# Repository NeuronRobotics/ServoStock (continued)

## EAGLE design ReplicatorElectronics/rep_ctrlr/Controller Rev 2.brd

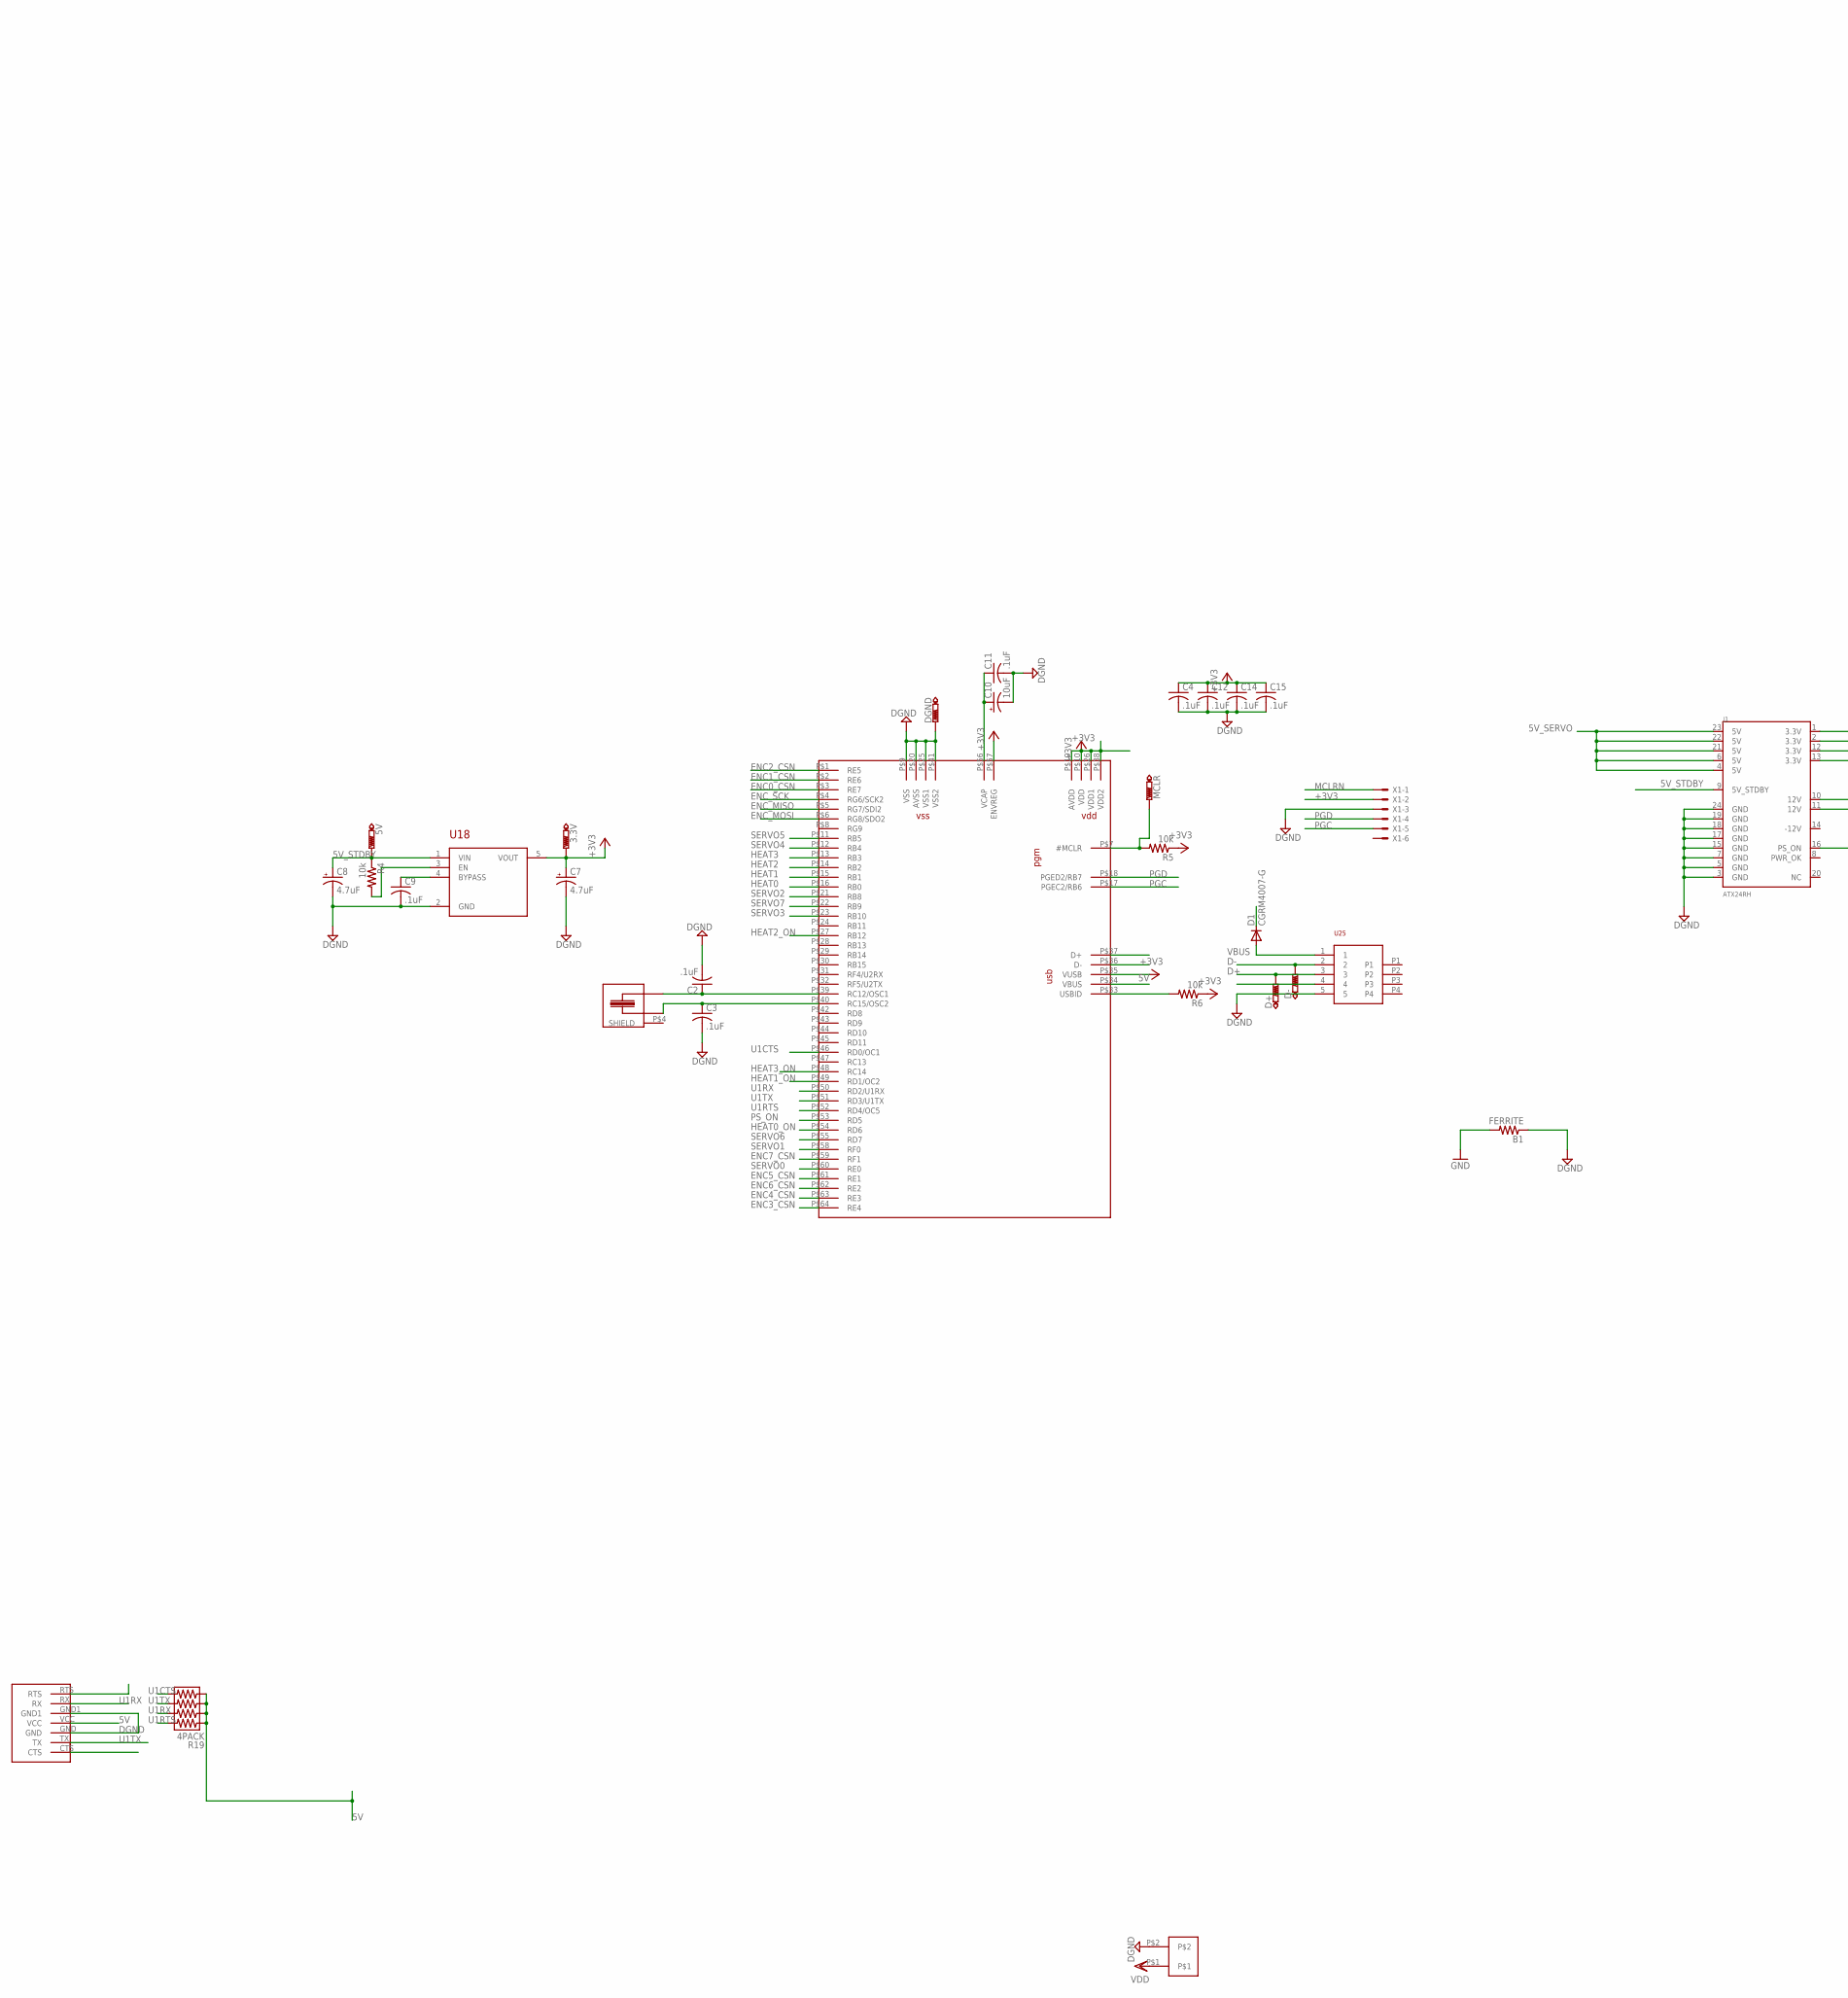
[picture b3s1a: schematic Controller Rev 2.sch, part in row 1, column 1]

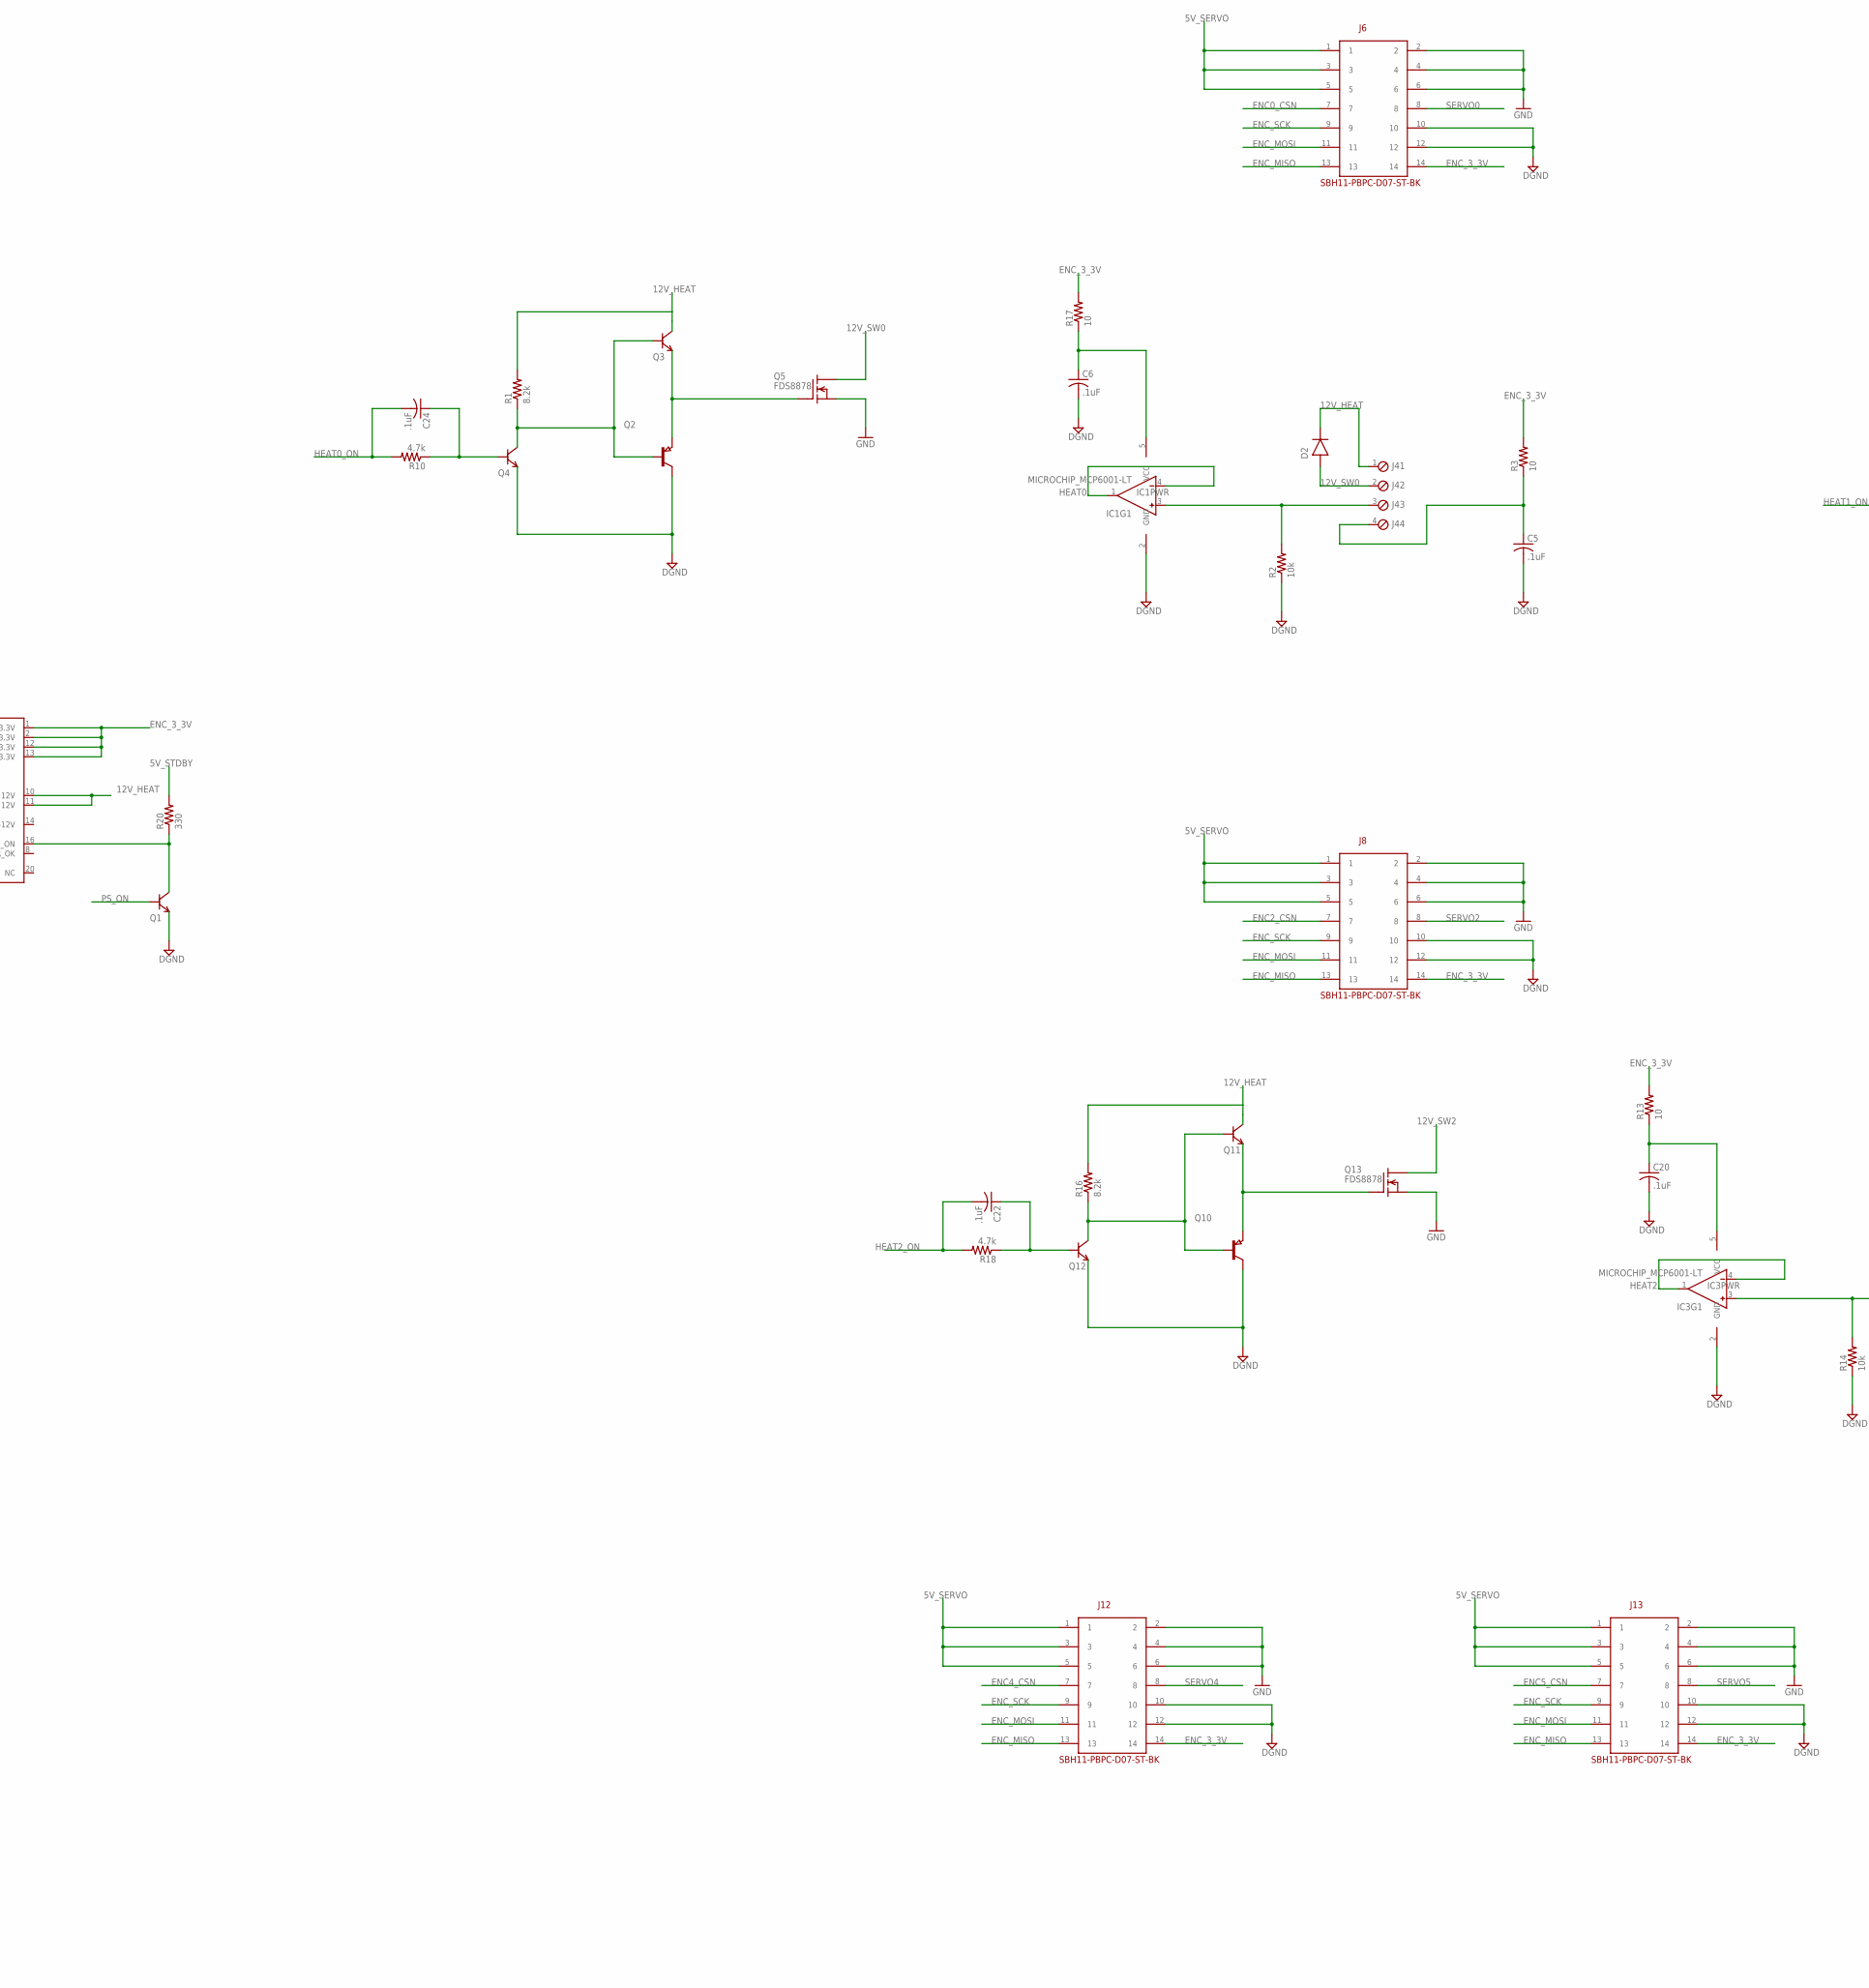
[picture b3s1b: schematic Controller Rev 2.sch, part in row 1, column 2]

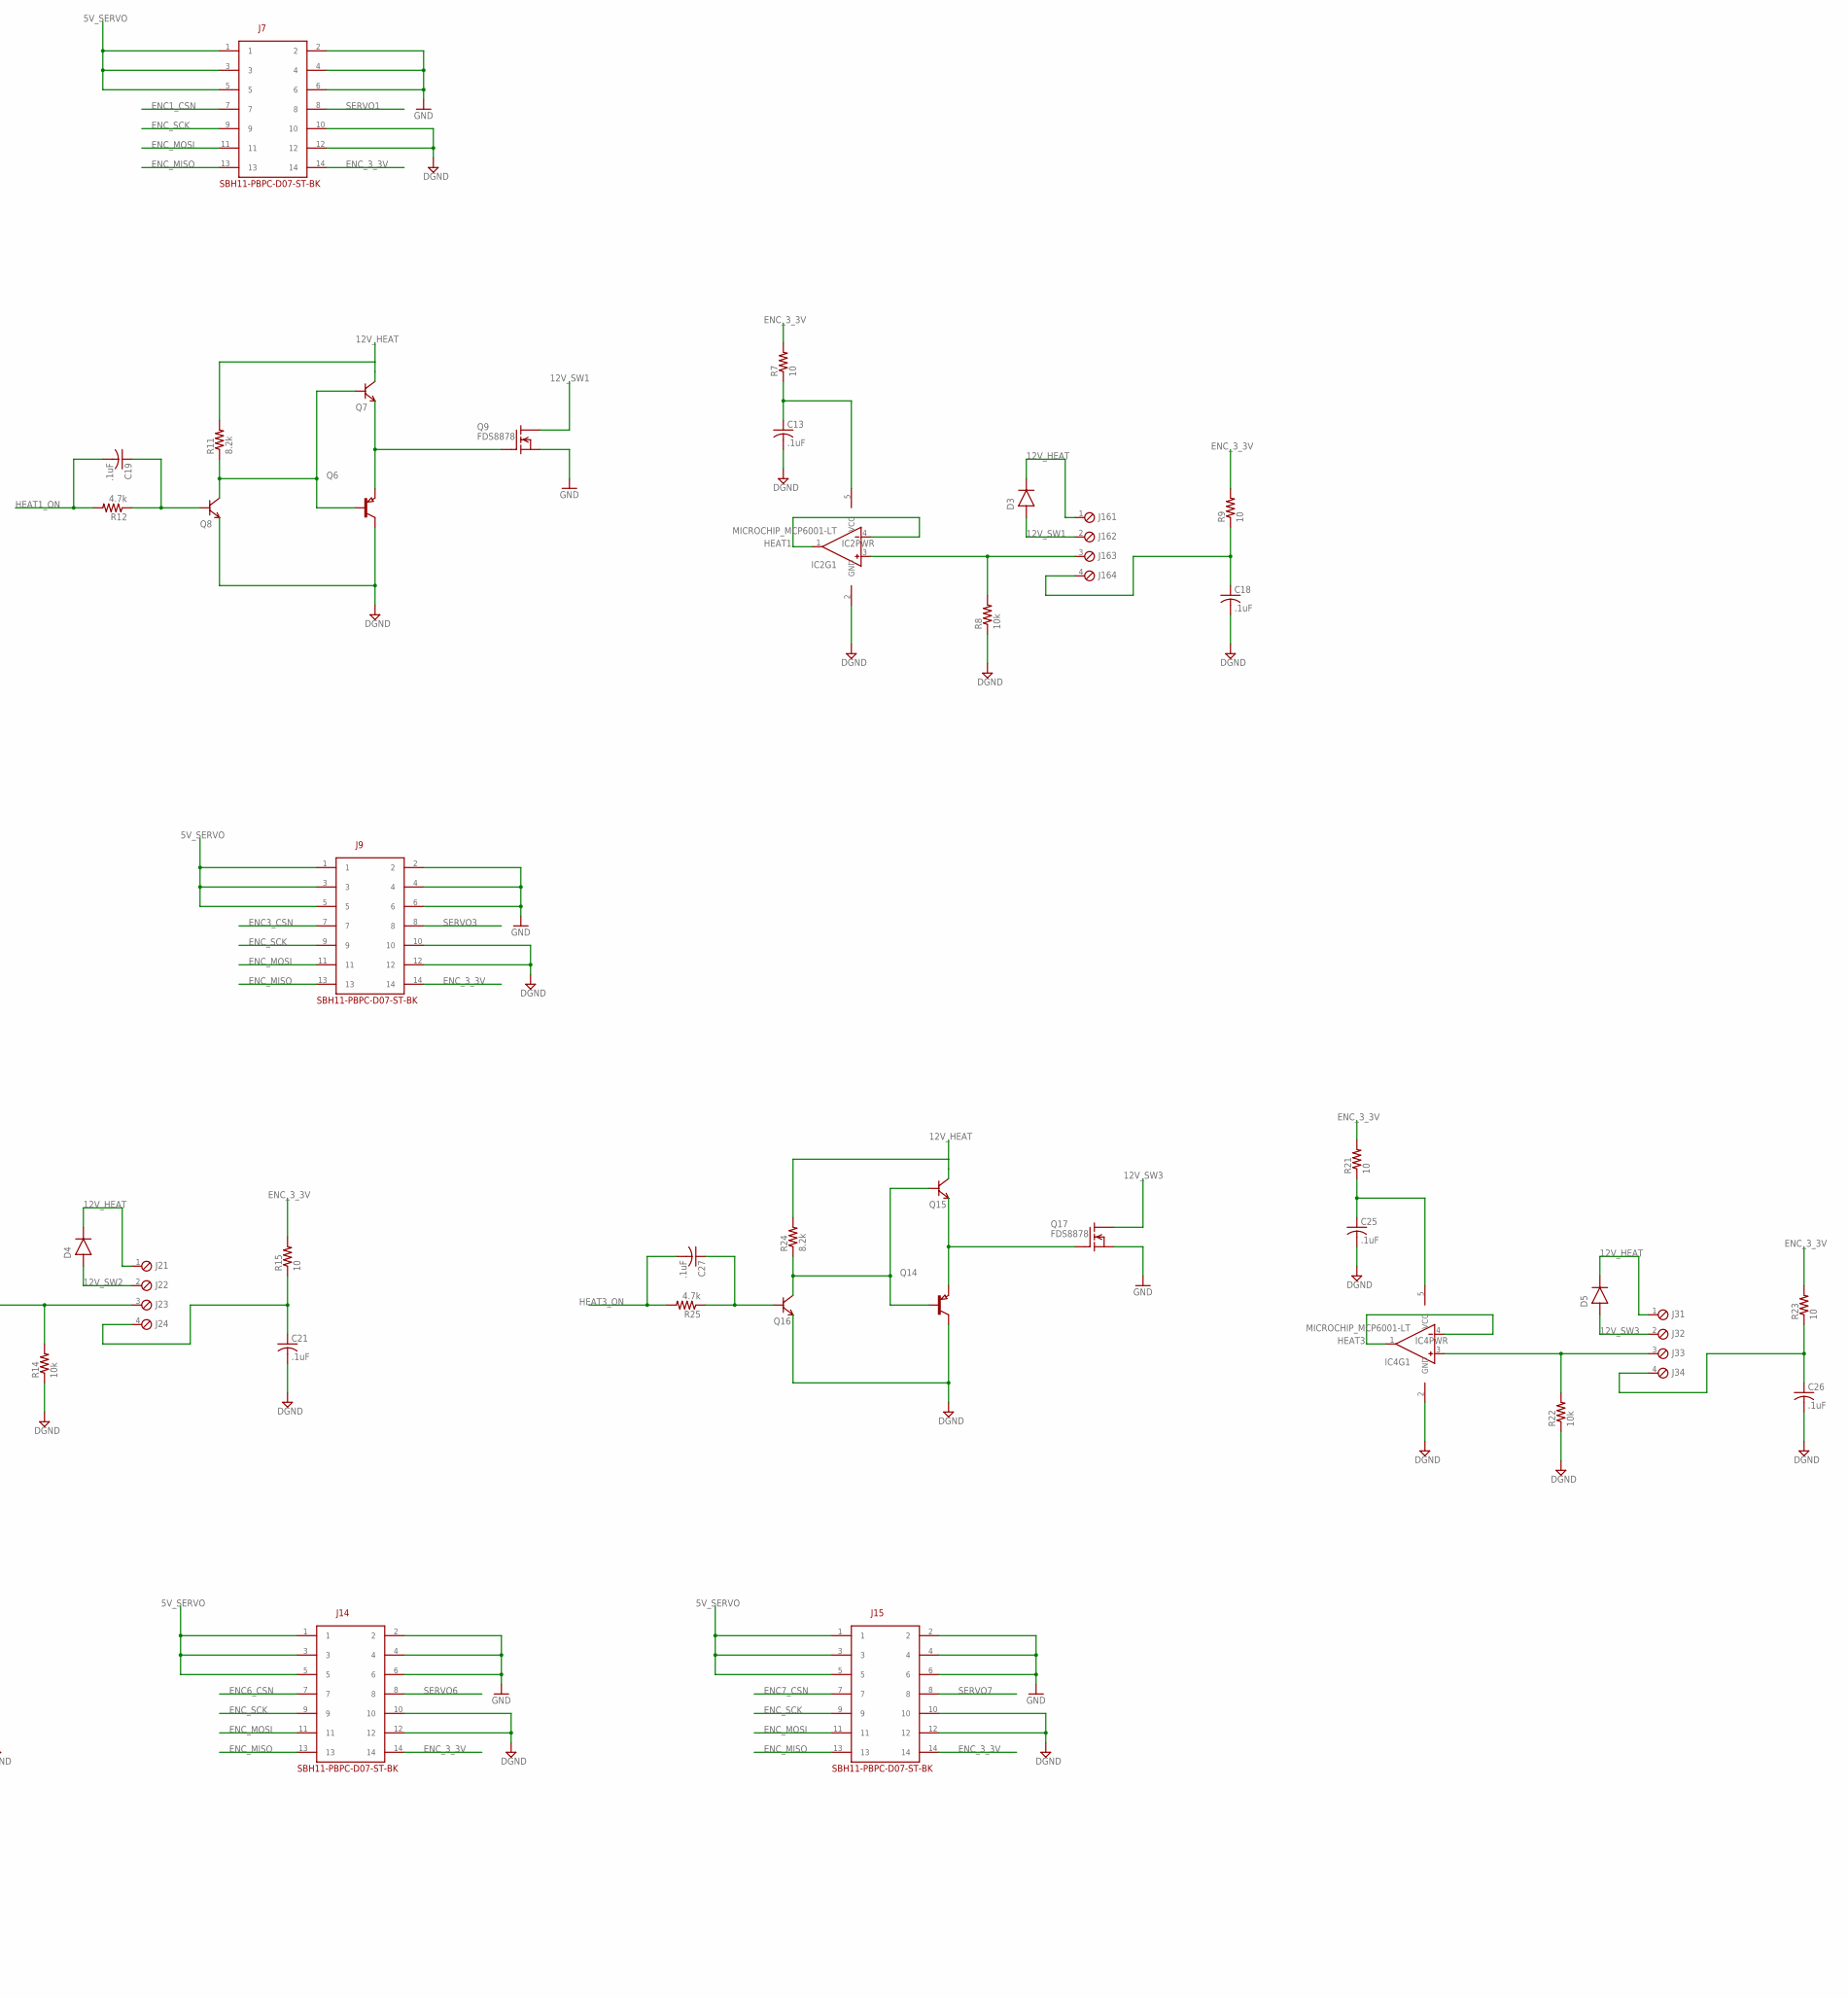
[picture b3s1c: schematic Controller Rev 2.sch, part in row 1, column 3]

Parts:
3.3V, 5V: PTR1TP14R; TP14R
B1: FERRITE; R0603
C2, C3, C4, C5, C6, C11, C12, C13, C14, C15, C18, C19, C20, C21, C22, C24, C25, C26, C27: .1uF; C0603
C7, C8: 4.7uF; R/2012-12R
C9: .1uF; C0402
C10: 10uF; R/2012-12R
D1: CGRM4007-G; SOD-123_MINI-SMA
D2, D3, D4, D5: DISCRETE_DIODESMA; DISCRETE_SMA
D+: PTR1TP14R; TP14R
D-: PTR1TP14R; TP14R
DGND: PTR1B1,27; B1,27
IC1, IC2, IC3, IC4: MICROCHIP_MCP6001-LT; MICROCHIP_SC70-5-LT
J1: ATX24RH; ATX24_RIGHT_ANGLE
J2, J3, J4, J16: OSTVN04A150; 4POL254
J6, J7, J8, J9, J12, J13, J14, J15: SBH11-PBPC-D07-ST-BK
J10: WASP7PIN
MCLR: PTR1TP14R; TP14R
Q1, Q3, Q4, Q7, Q8, Q11, Q12, Q15, Q16: DISCRETE_MMBT3904LT1G; DISCRETE_SOT23
Q2, Q6, Q10, Q14: PNP-TRANSISTOR_SOT23; SOT23
Q5, Q9, Q13, Q17: FDS8878; SO-8
R1, R11, R16, R24: 8.2k; R0603
R2, R5, R6, R8, R14, R22: 10k; R0603
R3, R7, R9, R13, R15, R17, R21, R23: 10; R0603
R4: 10k; R0402
R10, R12, R18, R25: 4.7k; R0603
R19: 4PACK; 4PACK_0603
R20: 330; R0603
U3: PIC32-64TQFP64-2; TQFP64-2
U18: LDS3985XX33; SOT23-5
U25: 1734035-1_USB; 1734035-1_1734035
U$19: 2P; 2PTH
X1: 22-23-2061
X2: CMR3XXT; CMR309T

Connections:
5V: D1.C, J10.VCC, R19.R1B, R19.R2B, R19.R3B, R19.R4B, U3.P$34 (VBUS)
5V_SERVO: J1.4 (5V), J1.6 (5V), J1.21 (5V), J1.22 (5V), J1.23 (5V), J6.1, J6.3, J6.5, J7.1, J7.3, J7.5, J8.1, J8.3, J8.5, J9.1, J9.3, J9.5, J12.1, J12.3, J12.5, J13.1, J13.3, J13.5, J14.1, J14.3, J14.5, J15.1, J15.3, J15.5
5V_STDBY: 5V.TP, C8.+, J1.9 (5V_STDBY), R4.1, R20.2, U18.1 (VIN)
12V_HEAT: D2.C, D3.C, D4.C, D5.C, J1.10 (12V), J1.11 (12V), J2.1, J3.1, J4.1, J16.1, Q3.3 (C), Q7.3 (C), Q11.3 (C), Q15.3 (C), R1.2, R11.2, R16.2, R24.2
12V_SW0: D2.A, J4.2, Q5.5 (D), Q5.6 (D), Q5.7 (D), Q5.8 (D)
12V_SW1: D3.A, J16.2, Q9.5 (D), Q9.6 (D), Q9.7 (D), Q9.8 (D)
12V_SW2: D4.A, J2.2, Q13.5 (D), Q13.6 (D), Q13.7 (D), Q13.8 (D)
12V_SW3: D5.A, J3.2, Q17.5 (D), Q17.6 (D), Q17.7 (D), Q17.8 (D)
+3V3: 3.3V.TP, C4.1, C7.+, C12.1, C14.1, C15.1, R5.1, R6.1, U3.P$10 (VDD), U3.P$19 (AVDD), U3.P$26 (VDD1), U3.P$35 (VUSB), U3.P$38 (VDD2), U3.P$57 (ENVREG), U18.5 (VOUT), X1.2
D+: D+.TP, U3.P$37 (D+), U25.3
D-: D-.TP, U3.P$36 (D-), U25.2
DGND: B1.1, C2.2, C3.2, C4.2, C5.2, C6.2, C7.-, C8.-, C9.2, C10.-, C11.2, C12.2, C13.2, C14.2, C15.2, C18.2, C20.2, C21.2, C25.2, C26.2, DGND.PP, IC1.2 (GND), IC2.2 (GND), IC3.2 (GND), IC4.2 (GND), J1.3 (GND), J1.5 (GND), J1.7 (GND), J1.15 (GND), J1.17 (GND), J1.18 (GND), J1.19 (GND), J1.24 (GND), J6.10, J6.12, J7.10, J7.12, J8.10, J8.12, J9.10, J9.12, J10.GND, J10.GND1, J12.10, J12.12, J13.10, J13.12, J14.10, J14.12, J15.10, J15.12, Q1.2 (E), Q2.3 (C), Q4.2 (E), Q6.3 (C), Q8.2 (E), Q10.3 (C), Q12.2 (E), Q14.3 (C), Q16.2 (E), R2.1, R8.1, R14.1, R22.1, U3.P$9 (VSS), U3.P$20 (AVSS), U3.P$25 (VSS1), U3.P$41 (VSS2), U18.2 (GND), U25.5, U$19.P$2, X1.3
ENC0_CSN: J6.7, U3.P$3 (RE7)
ENC1_CSN: J7.7, U3.P$2 (RE6)
ENC2_CSN: J8.7, U3.P$1 (RE5)
ENC3_CSN: J9.7, U3.P$64 (RE4)
ENC4_CSN: J12.7, U3.P$63 (RE3)
ENC5_CSN: J13.7, U3.P$61 (RE1)
ENC6_CSN: J14.7, U3.P$62 (RE2)
ENC7_CSN: J15.7, U3.P$59 (RF1)
ENC_3_3V: J1.1 (3.3V), J1.2 (3.3V), J1.12 (3.3V), J1.13 (3.3V), J6.14, J7.14, J8.14, J9.14, J12.14, J13.14, J14.14, J15.14, R3.2, R7.2, R9.2, R13.2, R15.2, R17.2, R21.2, R23.2
ENC_MISO: J6.13, J7.13, J8.13, J9.13, J12.13, J13.13, J14.13, J15.13, U3.P$5 (RG7/SDI2)
ENC_MOSI: J6.11, J7.11, J8.11, J9.11, J12.11, J13.11, J14.11, J15.11, U3.P$6 (RG8/SDO2)
ENC_SCK: J6.9, J7.9, J8.9, J9.9, J12.9, J13.9, J14.9, J15.9, U3.P$4 (RG6/SCK2)
GND: B1.2, J6.2, J6.4, J6.6, J7.2, J7.4, J7.6, J8.2, J8.4, J8.6, J9.2, J9.4, J9.6, J12.2, J12.4, J12.6, J13.2, J13.4, J13.6, J14.2, J14.4, J14.6, J15.2, J15.4, J15.6, Q5.1 (S), Q5.2 (S), Q5.3 (S), Q9.1 (S), Q9.2 (S), Q9.3 (S), Q13.1 (S), Q13.2 (S), Q13.3 (S), Q17.1 (S), Q17.2 (S), Q17.3 (S)
HEAT0: IC1.1 (OUT), IC1.4 (IN-), U3.P$16 (RB0)
HEAT0_ON: C24.2, R10.2, U3.P$54 (RD6)
HEAT1: IC2.1 (OUT), IC2.4 (IN-), U3.P$15 (RB1)
HEAT1_ON: C19.2, R12.2, U3.P$49 (RD1/OC2)
HEAT2: IC3.1 (OUT), IC3.4 (IN-), U3.P$14 (RB2)
HEAT2_ON: C22.2, R18.2, U3.P$27 (RB12)
HEAT3: IC4.1 (OUT), IC4.4 (IN-), U3.P$13 (RB3)
HEAT3_ON: C27.2, R25.2, U3.P$48 (RC14)
MCLRN: MCLR.TP, R5.2, U3.P$7 (#MCLR), X1.1
unnamed: C5.1, J4.4, R3.1
unnamed: R4.2, U18.3 (EN)
unnamed: C9.1, U18.4 (BYPASS)
unnamed: C3.1, U3.P$40 (RC15/OSC2), X2.P$3
unnamed: C10.+, C11.1, U3.P$56 (VCAP)
unnamed: C2.1, U3.P$39 (RC12/OSC1), X2.P$1
unnamed: IC2.3 (IN+), J16.3, R8.2
unnamed: C13.1, IC2.5 (VCC), R7.1
unnamed: C18.1, J16.4, R9.1
unnamed: IC1.3 (IN+), J4.3, R2.2
unnamed: Q6.1 (B), Q7.1 (B), Q8.3 (C), R11.1
unnamed: C19.1, Q8.1 (B), R12.1
unnamed: Q2.1 (B), Q3.1 (B), Q4.3 (C), R1.1
unnamed: C24.1, Q4.1 (B), R10.1
unnamed: Q6.2 (E), Q7.2 (E), Q9.4 (G)
unnamed: Q2.2 (E), Q3.2 (E), Q5.4 (G)
unnamed: IC3.3 (IN+), J2.3, R14.2
unnamed: C20.1, IC3.5 (VCC), R13.1
unnamed: C21.1, J2.4, R15.1
unnamed: Q10.1 (B), Q11.1 (B), Q12.3 (C), R16.1
unnamed: C6.1, IC1.5 (VCC), R17.1
unnamed: C22.1, Q12.1 (B), R18.1
unnamed: Q10.2 (E), Q11.2 (E), Q13.4 (G)
unnamed: IC4.3 (IN+), J3.3, R22.2
unnamed: C25.1, IC4.5 (VCC), R21.1
unnamed: C26.1, J3.4, R23.1
unnamed: Q14.1 (B), Q15.1 (B), Q16.3 (C), R24.1
unnamed: C27.1, Q16.1 (B), R25.1
unnamed: Q14.2 (E), Q15.2 (E), Q17.4 (G)
unnamed: J1.16 (PS_ON), Q1.3 (C), R20.1
PGC: U3.P$17 (PGEC2/RB6), X1.5
PGD: U3.P$18 (PGED2/RB7), X1.4
PS_ON: Q1.1 (B), U3.P$53 (RD5)
SERVO0: J6.8, U3.P$60 (RE0)
SERVO1: J7.8, U3.P$58 (RF0)
SERVO2: J8.8, U3.P$21 (RB8)
SERVO3: J9.8, U3.P$23 (RB10)
SERVO4: J12.8, U3.P$12 (RB4)
SERVO5: J13.8, U3.P$11 (RB5)
SERVO6: J14.8, U3.P$55 (RD7)
SERVO7: J15.8, U3.P$22 (RB9)
U1CTS: J10.CTS, R19.R4A, U3.P$46 (RD0/OC1)
U1RTS: J10.RTS, R19.R1A, U3.P$52 (RD4/OC5)
U1RX: J10.RX, R19.R2A, U3.P$50 (RD2/U1RX)
U1TX: J10.TX, R19.R3A, U3.P$51 (RD3/U1TX)
USBID: R6.2, U3.P$33 (USBID), U25.4
VBUS: D1.A, U25.1
VDD: U$19.P$1

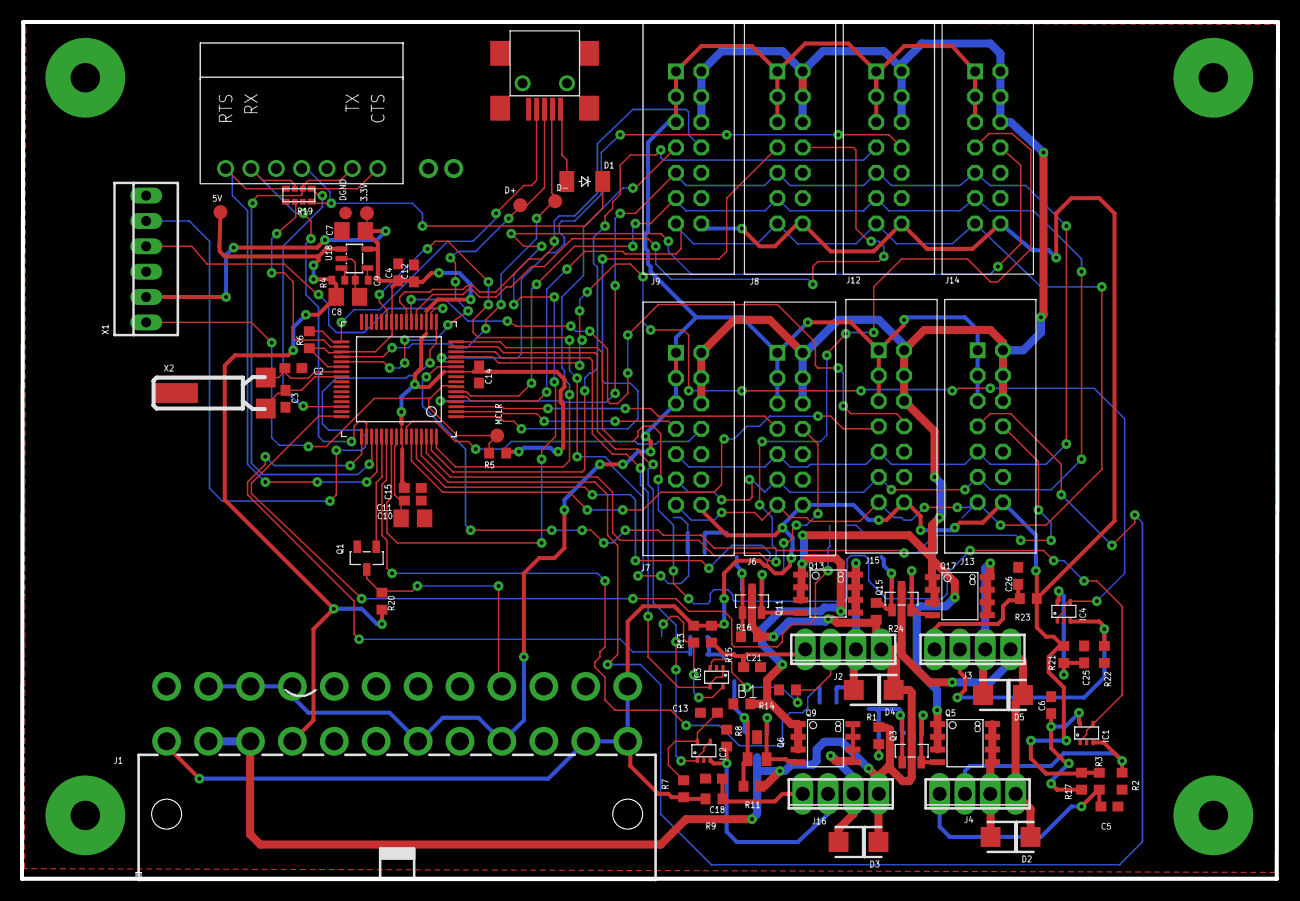
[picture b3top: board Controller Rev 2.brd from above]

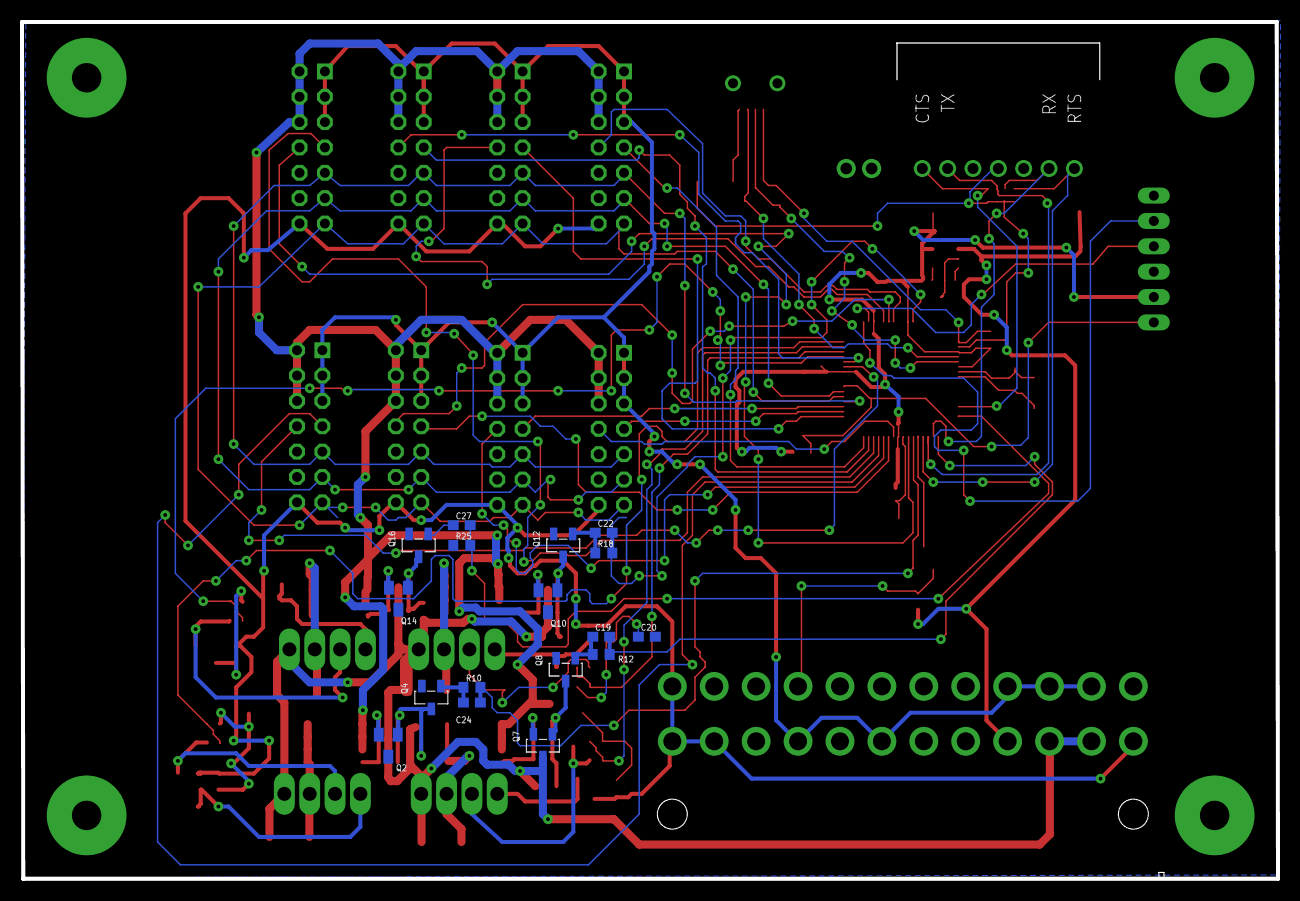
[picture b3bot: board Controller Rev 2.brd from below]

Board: 2 copper layers, 125.9 x 85.9 mm, 101 parts (17 on the bottom side), 81 nets.

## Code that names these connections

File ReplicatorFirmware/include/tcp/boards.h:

void initBackplaneHardware(void);
void initBackplanePowerMgmnt(void);
UINT16 Get5vRailVoltage(void);
UINT16 Get12vRailVoltage(void);
UINT16 Get48vRailVoltage(void);
void initBackplaneVoltageSenseRelays(void);

// This is a hack to deal with board E SPI short issue.
//#define swapEandF


// IO Mappigns for Relay Controll
#define Engaged             1
#define Disengaged          0

#define Relay5v             _RG14
#define Relay12v            _RA6
#define Relay48v            _RG14

#define Relay5_GPIO_TRIS    _TRISG14
#define Relay12_GPIO_TRIS   _TRISA6
#define Relay48_GPIO_TRIS   _RA7

//IO Mappings for Boards A-H

// Configure TRIS on all IO to the corrrect type
#define ConfigureCardIO()   {\
(BoardA_IRQ_TRIS)       =   INPUT;\
(BoardA_CS_TRIS)        =   OUTPUT;\
(BoardB_IRQ_TRIS)       =   INPUT;\
(BoardB_CS_TRIS)        =   OUTPUT;\
(BoardC_IRQ_TRIS)       =   INPUT;\
(BoardC_CS_TRIS)        =   OUTPUT;\
(BoardD_IRQ_TRIS)       =   INPUT;\
(BoardD_CS_TRIS)        =   OUTPUT;\
(BoardE_IRQ_TRIS)       =   INPUT;\
(BoardE_CS_TRIS)        =   OUTPUT;\
(BoardF_IRQ_TRIS)       =   INPUT;\
(BoardF_CS_TRIS)        =   OUTPUT;\
(BoardG_IRQ_TRIS)       =   INPUT;\
(BoardG_CS_TRIS)        =   OUTPUT;\
(BoardH_IRQ_TRIS)       =   INPUT;\
(BoardH_CS_TRIS)        =   OUTPUT;\
(BoardA_Detect_TRIS)    =   INPUT;\
(BoardB_Detect_TRIS)    =   INPUT;\
(BoardC_Detect_TRIS)    =   INPUT;\
(BoardD_Detect_TRIS)    =   INPUT;\
(BoardE_Detect_TRIS)    =   INPUT;\
(BoardF_Detect_TRIS)    =   INPUT;\
(BoardG_Detect_TRIS)    =   INPUT;\
(BoardH_Detect_TRIS)    =   INPUT;\
}  

// De-Select all cards
#define CardCSSelectNone(){\
(BoardA_CS) =   NOT_ASSERTED;\
(BoardB_CS) =   NOT_ASSERTED;\
(BoardC_CS) =   NOT_ASSERTED;\
(BoardD_CS) =   NOT_ASSERTED;\
(BoardE_CS) =   NOT_ASSERTED;\
(BoardF_CS) =   NOT_ASSERTED;\
(BoardG_CS) =   NOT_ASSERTED;\
(BoardH_CS) =   NOT_ASSERTED;\
}




// GPIO Mappings
#define BoardA_CS_TRIS      _TRISE7
#define BoardA_IRQ_TRIS       _TRISG13
#define BoardA_CS           _RE7
#define BoardA_IRQ          _RG13

#define BoardB_CS_TRIS      _TRISE6
#define BoardB_IRQ_TRIS       _TRISG0
#define BoardB_CS           _RE6
#define BoardB_IRQ          _RG0

#define BoardC_CS_TRIS      _TRISE5
#define BoardC_IRQ_TRIS       _TRISG1
#define BoardC_CS           _RE5
#define BoardC_IRQ          _RG1

#define BoardD_CS_TRIS      _TRISE4
#define BoardD_IRQ_TRIS     _TRISF1
#define BoardD_CS           _RE4
#define BoardD_IRQ          _RF1


#ifdef swapEandF
    #define BoardF_CS_TRIS      _TRISE3
    #define BoardF_IRQ_TRIS     _TRISF0
    #define BoardF_CS           _RE3
    #define BoardF_IRQ          _RF0

    #define BoardE_CS_TRIS      _TRISE2
    #define BoardE_IRQ_TRIS      _TRISD2
    #define BoardE_CS           _RE2
    #define BoardE_IRQ          _RD2
#else
    #define BoardE_CS_TRIS      _TRISE3
    #define BoardE_IRQ_TRIS     _TRISF0
    #define BoardE_CS           _RE3
    #define BoardE_IRQ          _RF0

    #define BoardF_CS_TRIS      _TRISE2
    #define BoardF_IRQ_TRIS      _TRISD2
    #define BoardF_CS           _RE2
    #define BoardF_IRQ          _RD2
#endif

#define BoardG_CS_TRIS      _TRISE1
#define BoardG_IRQ_TRIS     _TRISD13
#define BoardG_CS           _RE1
#define BoardG_IRQ          _RD13

#define BoardH_CS_TRIS      _TRISE0
#define BoardH_IRQ_TRIS      _TRISD6
#define BoardH_CS           _RE0
#define BoardH_IRQ          _RD6

// Card Detect
#define BoardA_Detect_TRIS  _TRISC2
#define BoardA_Detect       _RC2
#define BoardB_Detect_TRIS  _TRISC1
#define BoardB_Detect       _RC1
#define BoardC_Detect_TRIS  _TRISG7
#define BoardC_Detect       _RG7
#define BoardD_Detect_TRIS  _TRISG6
#define BoardD_Detect       _RG6

#ifdef swapEandF
    #define BoardF_Detect_TRIS  _TRISC4
    #define BoardF_Detect       _RC4
    #define BoardE_Detect_TRIS  _TRISC3
    #define BoardE_Detect       _RC3
#else
    #define BoardE_Detect_TRIS  _TRISC4
    #define BoardE_Detect       _RC4
    #define BoardF_Detect_TRIS  _TRISC3
    #define BoardF_Detect       _RC3
#endif
#define BoardG_Detect_TRIS  _TRISF5
#define BoardG_Detect       _RF5
#define BoardH_Detect_TRIS  _TRISF4
#define BoardH_Detect       _RF4

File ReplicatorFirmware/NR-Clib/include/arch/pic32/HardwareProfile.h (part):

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
#if !defined(RED_LED_TRIS)
	#define RED_LED_TRIS		(_TRISB3)	//
	#define RED_LED_IO			(_RB3)

	#define GREEN_LED_TRIS		(_TRISB2)	//
	#define GREEN_LED_IO		(_RB2)

	#define BLUE_LED_TRIS		(_TRISB1)	//
	#define BLUE_LED_IO			(_RB1)
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	#define SET_RED(a)			(a==0?PORTSetBits(IOPORT_B,BIT_3):PORTClearBits(IOPORT_B,BIT_3))
	#define SET_GREEN(a)		(a==0?PORTSetBits(IOPORT_B,BIT_2):PORTClearBits(IOPORT_B,BIT_2))
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#endif

	#define FLAG_BUSY_TRIS			(_TRISD5)
	#define	FLAG_BUSY				(_RD5)
	#define FLAG_ASYNC_TRIS			(_TRISD7)
	#define FLAG_ASYNC				(_RD7)
	#define Init_FLAG_BUSY_ASYNC()	FLAG_ASYNC_TRIS=INPUT;FLAG_BUSY_TRIS=INPUT;


	#define AVR_RST_TRIS		(_TRISE3)
	#define AVR_RST_IO			(_RE3)
	#define InitAVR_RST()	  	 mPORTEOpenDrainOpen(BIT_3);AVR_RST_IO=0;
	//#define InitAVR_RST()	  	 mPORTEOpenDrainOpen(BIT_3);AVR_RST_IO=1;

	#define SPI_SCK_IO			(_RG6)
	#define SPI_SDI_IO			(_RG7)
	#define SPI_SDI_TRIS		(_TRISG7)
	#define SPI_SDO_IO			(_RG8)
	#define InitSPI_AVR()		mPORTGOpenDrainOpen(BIT_8);mPORTGOpenDrainOpen(BIT_6);SPI_SCK_IO=1;SPI_SDO_IO=1;SPI_SDI_TRIS=INPUT;

	#define RTS_HO_TRIS			(_TRISD4)
	#define	RTS_HO_IO			(_RD4)
	#define CTS_HO_TRIS			(_TRISD0)
	#define CTS_HO_IO			(_RD0)
	#define InitCTS_RTS_HO()	mPORTDOpenDrainOpen(BIT_4);CTS_HO_TRIS=INPUT;RTS_HO_IO=NOT_ASSERTED;

	#define UART2TX_TRIS		(_TRISF5)
	#define UART2TX_IO			(_RF5)
	#define UART2RX_TRIS		(_TRISF4)
	#define UART2RX_IO			(_RF4)

	#define UART1TX_TRIS		(_TRISD3)
	#define UART1TX_IO			(_RD3)
	#define UART1RX_TRIS		(_TRISD2)
	#define UART1RX_IO			(_RD2)
	#define ConfigUARTOpenCollector()	mPORTDOpenDrainOpen(BIT_3); mPORTFOpenDrainOpen(BIT_5);
	#define ConfigUARTRXTristate()	UART1RX_TRIS=INPUT;UART2RX_TRIS=INPUT;
	#define InitBankLEDs()
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
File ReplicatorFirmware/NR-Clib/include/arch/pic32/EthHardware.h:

/*********************************************************************
 *
 *	Hardware specific definitions
 *
 *********************************************************************
 * FileName:        HardwareProfile.h
 * Dependencies:    None
 * Processor:       PIC18, PIC24F, PIC24H, dsPIC30F, dsPIC33F, PIC32
 * Compiler:        Microchip C32 v1.10 or higher
 *					Microchip C30 v3.12 or higher
 *					Microchip C18 v3.34 or higher
 *					HI-TECH PICC-18 PRO 9.63PL2 or higher
 * Company:         Microchip Technology, Inc.
 *
 * Software License Agreement
 *
 * Copyright (C) 2002-2010 Microchip Technology Inc.  All rights
 * reserved.
 *
 * Microchip licenses to you the right to use, modify, copy, and
 * distribute:
 * (i)  the Software when embedded on a Microchip microcontroller or
 *      digital signal controller product ("Device") which is
 *      integrated into Licensee's product; or
 * (ii) ONLY the Software driver source files ENC28J60.c, ENC28J60.h,
 *		ENCX24J600.c and ENCX24J600.h ported to a non-Microchip device
 *		used in conjunction with a Microchip ethernet controller for
 *		the sole purpose of interfacing with the ethernet controller.
 *
 * You should refer to the license agreement accompanying this
 * Software for additional information regarding your rights and
 * obligations.
 *
 * THE SOFTWARE AND DOCUMENTATION ARE PROVIDED "AS IS" WITHOUT
 * WARRANTY OF ANY KIND, EITHER EXPRESS OR IMPLIED, INCLUDING WITHOUT
 * LIMITATION, ANY WARRANTY OF MERCHANTABILITY, FITNESS FOR A
 * PARTICULAR PURPOSE, TITLE AND NON-INFRINGEMENT. IN NO EVENT SHALL
 * MICROCHIP BE LIABLE FOR ANY INCIDENTAL, SPECIAL, INDIRECT OR
 * CONSEQUENTIAL DAMAGES, LOST PROFITS OR LOST DATA, COST OF
 * PROCUREMENT OF SUBSTITUTE GOODS, TECHNOLOGY OR SERVICES, ANY CLAIMS
 * BY THIRD PARTIES (INCLUDING BUT NOT LIMITED TO ANY DEFENSE
 * THEREOF), ANY CLAIMS FOR INDEMNITY OR CONTRIBUTION, OR OTHER
 * SIMILAR COSTS, WHETHER ASSERTED ON THE BASIS OF CONTRACT, TORT
 * (INCLUDING NEGLIGENCE), BREACH OF WARRANTY, OR OTHERWISE.
 *
 *
 * Author               Date		Comment
 *~~~~~~~~~~~~~~~~~~~~~~~~~~~~~~~~~~~~~~~~~~~~~~~~~~~~~~~~~~~~~~~~~~~~
 * Howard Schlunder		10/03/06	Original, copied from Compiler.h
 * Ken Hesky            01/xx/10    Added MRF24WB0M-specific features
 ********************************************************************/
#ifndef __HARDWARE_PROFILE_H

#define PIC32_ENET_SK_DM320004		// PIC32MX795F512L Ethernet Starter Kit board with embedded Ethernet controller


// PIC32 Ethernet Starter Kit (04-02146) with PIC32MX795F512L processor and National DP83848 10/100 PHY
	// External SMSC PHY configuration
	#define	PHY_RMII				// external PHY runs in RMII mode
	#define	PHY_CONFIG_ALTERNATE	// alternate configuration used
	#define	PHY_ADDRESS			0x1	// the address of the National DP83848 PHY

    // Hardware mappings

	#define RED_LED_TRIS		LED0_TRIS	//
	#define RED_LED_IO			LED0_IO

	#define GREEN_LED_TRIS		LED1_TRIS	//
	#define GREEN_LED_IO		LED1_IO

	#define BLUE_LED_TRIS		LED2_TRIS	//
	#define BLUE_LED_IO			LED2_IO
	#define startLED()			mPORTDSetPinsDigitalOut(BIT_1|BIT_2|BIT_0)
	#define SET_RED(a)			(a==0?mPORTASetBits(BIT_0):mPORTAClearBits(BIT_0))
	#define SET_GREEN(a)		(a==0?mPORTASetBits(BIT_2):mPORTAClearBits(BIT_2))
	#define SET_BLUE(a)			(a==0?mPORTASetBits(BIT_1):mPORTAClearBits(BIT_1))

    #define LED0_TRIS			(TRISDbits.TRISD0)	// Ref LED1
	#define LED0_IO				(LATDbits.LATD0)
	#define LED1_TRIS			(TRISDbits.TRISD1)	// Ref LED2
	#define LED1_IO				(LATDbits.LATD1)
	#define LED2_TRIS			(TRISDbits.TRISD2)	// Ref LED3
	#define LED2_IO				(LATDbits.LATD2)

	#define LED3_TRIS			(LED2_TRIS)			// No such LED
	#define LED3_IO				(LATDbits.LATD6)
	#define LED4_TRIS			(LED2_TRIS)			// No such LED
	#define LED4_IO				(LATDbits.LATD6)
	#define LED5_TRIS			(LED2_TRIS)			// No such LED
	#define LED5_IO				(LATDbits.LATD6)
	#define LED6_TRIS			(LED2_TRIS)			// No such LED
	#define LED6_IO				(LATDbits.LATD6)
	#define LED7_TRIS			(LED2_TRIS)			// No such LED
	#define LED7_IO				(LATDbits.LATD6)

	#define LED_GET()			((BYTE)LATD & 0x07)
	#define LED_PUT(a)			do{LATD = (LATD & 0xFFF8) | ((a)&0x07);}while(0)

    #define BUTTON0_TRIS		(TRISDbits.TRISD6)	// Ref SW1
	#define	BUTTON0_IO			(PORTDbits.RD6)
	#define BUTTON1_TRIS		(TRISDbits.TRISD7)	// Ref SW2
	#define	BUTTON1_IO			(PORTDbits.RD7)
	#define BUTTON2_TRIS		(TRISDbits.TRISD13)	// Ref SW3
	#define	BUTTON2_IO			(PORTDbits.RD13)
	#define BUTTON3_TRIS		(TRISDbits.TRISD13)	// No BUTTON3 on this board
	#define	BUTTON3_IO			(1)
#if !defined(INPUT)
	#define INPUT 					1
#endif
	//Set buttons to be inputs and enable the weak pull-ups
	#define initButtons()       BUTTON0_TRIS=INPUT;BUTTON1_TRIS=INPUT;BUTTON2_TRIS=INPUT;CNPUESET=0x00098000;

	// Select which UART the STACK_USE_UART and STACK_USE_UART2TCP_BRIDGE
	// options will use.  You can change these to U1BRG, U1MODE, etc. if you
	// want to use the UART1 module instead of UART2.
	#define UBRG					U2BRG
	#define UMODE					U2MODE
	#define USTA					U2STA
	#define BusyUART()				BusyUART2()
	#define CloseUART()				CloseUART2()
	#define ConfigIntUART(a)		ConfigIntUART2(a)
	#define DataRdyUART()			DataRdyUART2()
	#define OpenUART(a,b,c)			OpenUART2(a,b,c)
	#define ReadUART()				ReadUART2()
	#define WriteUART(a)			WriteUART2(a)
	#define getsUART(a,b,c)			getsUART2(a,b,c)
	#if defined(__C32__)
		#define putsUART(a)			putsUART2(a)
	#else
		#define putsUART(a)			putsUART2((unsigned int*)a)
	#endif
	#define getcUART()				getcUART2()
	#define putcUART(a)				do{while(BusyUART()); WriteUART(a); while(BusyUART()); }while(0)
	#define putrsUART(a)			putrsUART2(a)


#endif
